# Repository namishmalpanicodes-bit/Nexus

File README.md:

# Nexus
Nexus is a smart desktop control centre. You have all your data from the task manager directly in front of you, like CPU, GPU, RAM, and storage one click and you know which app is consuming how Ram or storage. We also have a sidebar where we have features like notifications, screen time, and modes.

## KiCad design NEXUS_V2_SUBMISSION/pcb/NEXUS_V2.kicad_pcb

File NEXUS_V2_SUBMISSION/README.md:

# NEXUS V2 – desk control panel

NEXUS V2 is a desk control panel in the spirit of a Stream Deck. It has a 7" touchscreen, six programmable keys and a volume knob, and connects to a Mac or PC with a single USB-C cable. It is built around an **ESP32-P4** on a custom 4-layer PCB. No dev board is used.

## What it is and how to use it

1. Plug NEXUS into your computer with one USB-C cable. That single cable provides both power and data.
2. **Six keys (2 × 3):** each one triggers a computer shortcut. The firmware sends F13–F18, and the companion app maps each one to any action (launch an app, mute the mic, run a macro…).
3. **Knob:** turn it to change the volume and press it to mute or unmute.
4. **7" touchscreen:** shows CPU / RAM / GPU / storage, per-app usage, screen time and notifications. The sidebar switches between modes: **Coding, Study, Focus, Calm** (customisable).
5. **Tilt:** the screen sits on a weighted base with friction hinges. Tilt it to any angle from 15° to 70° and it stays there.

## Why I made it

I made NEXUS because I was struggling with small daily tasks. While browsing the internet, if I wanted to check my CPU, RAM, storage or any usage, I had to leave my browser and open Task Manager. To check my screen time, I had to go through Settings. To check my notifications, I had to open my phone or Gmail. And my device didn't have modes at all. That's why I created NEXUS.

Everything is in front of you: your CPU, GPU, RAM and storage. Click once and it tells you which app is using what. You get different modes (coding mode, study mode, focus mode, calm mode), and you can customise them however you want. Screen time shows you which app you used and for how long. You can enable notifications for any app you like, and disable them too.

## Hardware

| Block | Part |
|---|---|
| MCU | Espressif ESP32-P4NRW16X (QFN-104, 16 MB PSRAM) + 16 MB QSPI flash |
| Display | Waveshare 7-DSI-TOUCH-A, 720 × 1280 IPS, MIPI-DSI 2-lane, I2C touch |
| Keys | 6 × C&K PTS526 SPG15 SMTR2 LFS (320 gf), 19 mm pitch, pull-ups + firmware debounce |
| Encoder | EC11 incremental encoder with push switch |
| Power | USB-C 5 V → 2 × TLV62569 bucks (3V3 and VDD_HP core); internal LDOs for flash, PSRAM and MIPI |
| USB | HRO TYPE-C-31-M-12, USB 2.0 High-Speed to the ESP32-P4 OTG PHY |
| PCB | 54 × 118 mm, 4 layers (signal / GND / 3V3 / signal); KiCad DRC: 0 errors, 0 warnings, 0 unconnected |

## Enclosure

- **Form:** a slab on a stand. The screen is on the left and the keys and knob are on the right. The PCB sits *beside* the display, so the slab is only as thick as the display.
- **Base:** weighted with ~300 g of M12 steel washers in a pocket at the front. Two constant-torque hinges allow a 15–70° tilt.
- **USB-C plug:** an L-shaped plug sits hidden in a pocket in the base, and the cable exits at the rear.
- **CAD:** fully parametric Onshape FeatureScript (`cad/NEXUS_V2_slab_enclosure.fs`). Parameters: display depth, hinge hole spacing and screw size.
- **Printed parts (10):** front shell, back cover, base, 6 keycaps, 24 mm knob.
- **Materials:** matte PLA or PETG.

## Files

| Item | Location |
|---|---|
| STEP file for each part | `cad/NEXUS_V2_parts_STEP.zip` (10 parts) |
| Full assembly STEP | `cad/NEXUS_V2_full_assembly.step` |
| Onshape source | https://cad.onshape.com/documents/3eb919e14392e073160f8015/w/52b0d7887805c9e8dcde4446/e/a73d1369f3e2af2bd40e8e28 |
| KiCad project | `pcb/NEXUS_V2.kicad_pro`, `.kicad_sch`, `.kicad_pcb`, `.kicad_prl` + `NEXUS_V2_Custom.kicad_sym`, `NEXUS_V2_Footprints.pretty/`, `fp-lib-table`, `sym-lib-table` |
| Gerbers + drill | `pcb/gerbers.zip` |
| Firmware | `firmware/`: ESP-IDF project, untested (keys → F13–F18, knob → volume / mute) |
| BOM with links | `BOM.csv` |
| Pin map | `PIN_MAP.md` |
| Fabrication status | `pcb/FABRICATION_STATUS.txt` |

## Status and known issues (rev B)

- **Verified:** KiCad DRC is clean. The switch footprint was checked against the C&K datasheet. The encoder footprint matches the ALPS EC11 reference and the listing dimensions (6 mm D-shaft, M7 thread, 15 mm shaft, 15 × 12 mm body). The display outline and depth match the Waveshare drawing.
- **To confirm on the real parts before ordering boards:**
  - encoder pin spacing (caliper check)
  - display cable contact side, which decides the exact J1 connector part
  - hinge hole pattern
- **Rev C plan:**
  - rear-facing USB-C through the back cover
  - a branded encoder (Bourns PEC11R) for production
  - display UI firmware: MIPI-DSI + LVGL, plus a USB link to the companion app

## Bill of materials

Full list with links: [BOM.csv](BOM.csv). Prices in USD (INR prices converted at 1 USD = 94.85 INR).

| Product | Description | Link | Price (USD) |
|---|---|---|---|
| Display | Waveshare 7-DSI-TOUCH-A. 7in 720x1280 IPS MIPI-DSI touch display; includes DSI-Cable-12cm + 5V power cable. Already owned. | [link](https://zbotic.in/product/waveshare-7inch-dsi-capacitive-touch-display/) | 67.93 |
| Rotary encoder | FlyRobo EC11 15 mm half-shaft SKU 3370. Incremental encoder with push switch (volume / mute). Price = Rs 47 encoder + Rs 100 FlyRobo delivery. | [link](https://www.flyrobo.in/ec11-rotary-encoder-half-shaft-handle-potentiometer-15mm) | 1.55 |
| MCU | ESP32-P4NRW16X. Espressif ESP32-P4, QFN-104, 16 MB PSRAM in package | [link](https://www.lcsc.com/search?q=ESP32-P4NRW16X) | 4.74 |
| Flash | W25Q128JVSIQ. 16 MB QSPI flash, SOIC-8 208 mil | [link](https://www.lcsc.com/search?q=W25Q128JVSIQ) | 2.18 |
| Buck regulator x2 | TLV62569DBVR. 3 A step-down (core VDD_HP and 3V3) | [link](https://www.ti.com/product/TLV62569) | 0.13 |
| Inductor x2 | Murata DFE252012F-2R2M. 2.2 uH, Isat >= 3 A, 2520 | [link](https://www.lcsc.com/search?q=DFE252012F-2R2M) | 0.07 |
| Crystal | 40 MHz 3225. 40 MHz, CL 10 pF, +-10 ppm, 3225 | [link](https://www.lcsc.com/search?q=40MHz%203225%20crystal%2010pF) | 0.05 |
| USB-C receptacle | HRO TYPE-C-31-M-12. 16-pin USB 2.0 Type-C, LCSC C165948 | [link](https://lcsc.com/product-detail/C165948.html) | 0.10 |
| FPC connector | Amphenol SFW15R-1STAE1LF (or Molex 52207-1560). 15-pin 1.0 mm FPC ZIF (display DSI). Final pick depends on cable contact side | [link](https://lioncircuits.com/parts/SFW15R-1STE1LF) | 0.95 |
| Tactile switch x8 | C&K PTS526 SPG15 SMTR2 LFS, Robu SKU R185029, USD 0.14 each. 6 keys + BOOT and RESET. Robu delivery is free above Rs 999; below that it is added at checkout. | [link](https://robu.in/product/pts526-spg15-smtr2-lfs-ck-5-2mm-1-5mm-5-2mm-320gf-smd-tactile-switches-rohs/) | 1.10 |
| TVS diode | SMF5.0A. 5 V TVS on VBUS, SOD-123F | [link](https://www.lcsc.com/search?q=SMF5.0A) | 0.05 |
| ESD diode x2 | TI TPD1E0B04. 0.13 pF bidirectional ESD (USB D+/D-) | [link](https://www.lcsc.com/search?q=TPD1E0B04) | 0.33 |
| PTC fuse | Bourns MF-MSMF110. 1.1 A hold, 1812 | [link](https://www.lcsc.com/search?q=MF-MSMF110) | 0.03 |
| LED x2 | 0603 LED green / blue. Power and user LEDs | [link](https://www.lcsc.com/search?q=0603%20LED) | 0.03 |
| Capacitor 10uF x6 | 10uF 10V X5R 0805 | [link](https://www.lcsc.com/search?q=10uF%200805%2010V%20X5R) | 0.09 |
| Capacitor 22uF x3 | 22uF 10V X5R 0805 | [link](https://www.lcsc.com/search?q=22uF%200805%2010V) | 0.16 |
| Capacitor 4.7uF x2 | 4.7uF 10V X5R 0603 | [link](https://www.lcsc.com/search?q=4.7uF%200603%2010V) | 0.03 |
| Capacitor 1uF x6 | 1uF 10V X5R 0402 LCSC sells these in strips of 100, so the price is for 100 pcs. | [link](https://www.lcsc.com/search?q=1uF%200402%2010V) | 0.23 |
| Capacitor 0.1uF x23 | 0.1uF 16V X7R 0402 LCSC sells these in strips of 100, so the price is for 100 pcs. | [link](https://www.lcsc.com/search?q=100nF%200402%2016V%20X7R) | 0.16 |
| Capacitor 10nF x2 | 10nF 16V X7R 0402 LCSC sells these in strips of 100, so the price is for 100 pcs. | [link](https://www.lcsc.com/search?q=10nF%200402) | 0.16 |
| Capacitor 22pF | 22pF C0G 0402 LCSC sells these in strips of 100, so the price is for 100 pcs. | [link](https://www.lcsc.com/search?q=22pF%200402%20C0G) | 0.16 |
| Capacitor 15pF x2 | 15pF C0G 0402. Crystal load (tune) LCSC sells these in strips of 100, so the price is for 100 pcs. | [link](https://www.lcsc.com/search?q=15pF%200402%20C0G) | 0.16 |
| Resistor 10k x12 | 10k 1% 0402. Pull-ups (buttons, encoder, straps) LCSC sells these in strips of 100, so the price is for 100 pcs. | [link](https://www.lcsc.com/search?q=10k%200402%201%) | 0.05 |
| Resistor 5.1k x2 | 5.1k 1% 0402. USB-C CC pull-downs LCSC sells these in strips of 100, so the price is for 100 pcs. | [link](https://www.lcsc.com/search?q=5.1k%200402) | 0.05 |
| Resistor 2.2k x2 | 2.2k 0402. I2C pull-ups LCSC sells these in strips of 100, so the price is for 100 pcs. | [link](https://www.lcsc.com/search?q=2.2k%200402) | 0.05 |
| Resistor 1k x2 | 1k 0603. LED resistors LCSC sells these in strips of 100, so the price is for 100 pcs. | [link](https://www.lcsc.com/search?q=1k%200603) | 0.05 |
| Resistor (dividers) x6 | 453k / 100k / 499k x2 / 4.02k / 1M, 1% 0402. Buck feedback, DSI REXT, misc LCSC sells these in strips of 100, so the price is for 100 pcs. | [link](https://www.lcsc.com/search?q=0402%201%%20resistor) | 0.05 |
| Pin header 1x8 (J3) | Shekki 1x40 single-row male header, 2.54 mm, single strip. J3 programming header; cut 8 pins. | [link](https://www.amazon.in/dp/B0H467TGFM) | 0.52 |
| Pin header 1x3 right-angle (J4) | Electronic Spices 1x40 right-angle (90 deg) male header, pack of 5 (smallest pack on Amazon). J4 display 5 V header; cut 3 pins from one strip. | [link](https://www.amazon.in/dp/B0BG7KGL77) | 0.84 |
| PCB x5 | NEXUS V2 custom PCB rev B, 4-layer, 118 x 54 mm, 1.6 mm, ENIG. Manufacturing files: pcb/gerbers.zip in this repo (upload pcb/gerbers.zip at the JLCPCB link to get this exact quote: 5 pcs, 4 layers, ENIG = USD 84.00). JLCPCB minimum order is 5 boards; 1 is used, 4 are spares. | [link](https://cart.jlcpcb.com/quote) | 84.00 |
| Friction hinges | TAODAN torque friction hinges, 1 left + 1 right, mounting screws included. Holds the slab at any tilt angle. | [link](https://www.amazon.in/dp/B0BNH8985Y) | 23.21 |
| Base weight | 50 x M12 SS304 flat washers (DIN 125, about 6 g each, about 300 g total). Stacked in the pocket under the base to stop the device tipping. | [link](https://www.amazon.in/dp/B0H122NK8H) | 2.41 |
| Anti-slip feet | nuoshen clear self-adhesive rubber feet, 100 pcs (4 used under the base). | [link](https://www.amazon.in/dp/B0F7FKDTF9) | 1.17 |
| USB-C cable | Verilux 3 m USB-C to USB-C, 90 deg right-angle end, 480 Mbps data + 100 W. The L end plugs into NEXUS inside the base. | [link](https://www.amazon.in/dp/B0F942Z4LY) | 6.32 |
| 23AWG single-strand wire (black+red, 1+1 m) (tool) | CBL-QC0413. Assembly / testing tool. Already owned. | [link](https://quartzcomponents.com/search?q=CBL-QC0413) | 0.31 |
| Jumper wire combo M-M / M-F / F-F (10 each) (tool) | CBL-QC0613. Assembly / testing tool. Already owned. | [link](https://quartzcomponents.com/search?q=CBL-QC0613) | 0.65 |
| DT830D digital multimeter (tool) | TLS-QC0298. Assembly / testing tool. Already owned. | [link](https://quartzcomponents.com/search?q=TLS-QC0298) | 2.30 |
| MB102 breadboard 830 points (tool) | TLS-QC0412. Assembly / testing tool. Already owned. | [link](https://quartzcomponents.com/search?q=TLS-QC0412) | 0.85 |
| Solder wire 5 g (tool) x2 | TLS-QC0863. Assembly / testing tool. Already owned. | [link](https://quartzcomponents.com/search?q=TLS-QC0863) | 0.57 |
| RMA-223 solder flux paste (tool) | TLS-QC0864. Assembly / testing tool. Already owned. | [link](https://quartzcomponents.com/search?q=TLS-QC0864) | 0.46 |
| 25 W soldering iron (tool) | TLS-QC1041. Assembly / testing tool. Already owned. | [link](https://quartzcomponents.com/search?q=TLS-QC1041) | 1.03 |
| Soldering iron stand (tool) | TLS-QC2658. Assembly / testing tool. Already owned. | [link](https://quartzcomponents.com/search?q=TLS-QC2658) | 0.30 |
| Wire stripper / cutter 130 mm (tool) | TLS-QC3658. Assembly / testing tool. Already owned. | [link](https://quartzcomponents.com/search?q=TLS-QC3658) | 0.44 |
| SMT stencil | JLCPCB stencil, non-framework, top + bottom on one sheet, 0.12 mm, electropolished. Needed by the vendor to apply solder paste for the ESP32-P4 | [link](https://jlcpcb.com/pcb-stencil) | 7.00 |
| Double-sided foam tape | 3M Scotch heavy-duty double-sided foam tape (holds 4.5 kg per metre). Holds the display in the front shell and seals the washers into the base pocket. | [link](https://www.amazon.in/dp/B00N1U9AJS) | 1.80 |
| Shipping + customs (JLCPCB + LCSC) | PCBs, stencil and LCSC parts shipped from China in one combined parcel. Courier fee and Indian customs duty are calculated by JLCPCB/LCSC at checkout. | [link](https://jlcpcb.com) | At checkout |
| TOTAL build cost | Everything above except the tools and the shipping row. |  | 207.91 |
| Tools (already owned) | Not part of the build cost |  | 6.90 |

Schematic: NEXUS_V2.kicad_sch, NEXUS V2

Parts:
C1, C2, C9, C109, C110, C111: 10uF; C_0805; MPN 10uF 10V X5R 0805
C3, C10, C100, C101, C102, C103, C104, C105, C106, C107, C108, C112, C115, C116, C117, C118, C119, C121, C122, C125: 0.1uF; R_0402; MPN 0.1uF 16V X7R 0402
C4, C5, C7: 22uF; C_0805; MPN 22uF 10V X5R 0805
C6, C114: 4.7uF; R_0603; MPN 4.7uF 10V X5R 0603
C8: 22pF; R_0402; MPN 22pF C0G 0402
C11, C12: 15pF; R_0402; MPN 15pF C0G 0402 (tune)
C13, C120, C123, C124, C127, C128: 1uF; R_0402; MPN 1uF 10V X5R 0402
C14, C15, C16: 0.1uF; R_0402; MPN 0.1uF 0402
C113, C126: 10nF; R_0402; MPN 10nF 16V X7R 0402
D1: SMF5.0A; D_SOD123F; MPN SMF5.0A (5V TVS)
D2, D3: TPD1E0B04; R_0402; MPN TI TPD1E0B04 (0.13pF bidir ESD)
ENC1: EC11; MPN FlyRobo EC11 15 mm half-shaft SKU 3370 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
F1: PTC 1.1A; F_1812; MPN 1812 PTC 1.1A hold (e.g. Bourns MF-MSMF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
J1: DSI 15P; FPC15_P1.00mm_Generic; MPN 15p 1.0mm FPC ZIF (Hirose FH12-15S-1SH 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
J2: USB-C 16P; USB_C_HRO_TYPE-C-31-M-12_Recon; MPN HRO TYPE-C-31-M-12
J3: DEBUG; HDR_1x8; MPN 2.54mm 1x8 header - fit from BACK side 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
J4: DISP_5V; HDR_1x3; MPN 2.54mm 1x3 RIGHT-ANGLE header (display 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
L1: 2.2uH; L_2520; MPN 2.2uH Isat>=3A 2520 (e.g. Murata DFE252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
L2: 2.2uH; L_2520; MPN 2.2uH Isat>=3A 2520
LED1: LED 3V3; R_0603; MPN 0603 LED green
LED2: LED USER; R_0603; MPN 0603 LED blue
MH1, MH2, MH3, MH4: M3; MH_M3; MPN M3 mounting hole
R1, R2: 5.1k; R_0402; MPN 5.1k 1% 0402
R3: 453k; R_0402; MPN 453k 1% 0402
R4: 100k; R_0402; MPN 100k 1% 0402
R5, R15: 1k; R_0603; MPN 1k 0603
R6, R7: 499k; R_0402; MPN 499k 1% 0402
R8, R9, R10: 10k; R_0402; MPN 10k 0402
R11, R12: 2.2k; R_0402; MPN 2.2k 0402
R13: 4.02k; R_0402; MPN 4.02k 1% 0402
R14: 1M; R_0402; MPN 1M 0402
R16, R17, R18, R19, R20, R21: 10k; R_0402; MPN 10k 1% 0402 (button pull-up)
R22, R23, R24: 10k; R_0402; MPN 10k 1% 0402 (encoder pull-up)
SW1: BTN1; PTS526; MPN C&K PTS526 SPG15 SMTR2 LFS (320 gf, gro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
SW2: BTN2; PTS526; MPN C&K PTS526 SPG15 SMTR2 LFS (320 gf, gro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
SW3: BTN3; PTS526; MPN C&K PTS526 SPG15 SMTR2 LFS (320 gf, gro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
SW4: BTN4; PTS526; MPN C&K PTS526 SPG15 SMTR2 LFS (320 gf, gro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
SW5: BTN5; PTS526; MPN C&K PTS526 SPG15 SMTR2 LFS (320 gf, gro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
SW6: BTN6; PTS526; MPN C&K PTS526 SPG15 SMTR2 LFS (320 gf, gro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
SW7: BOOT; PTS526; MPN C&K PTS526 SPG15 SMTR2 LFS (320 gf, gro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
SW8: RESET; PTS526; MPN C&K PTS526 SPG15 SMTR2 LFS (320 gf, gro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
U1: ESP32-P4NRW16X; ESP32-P4_QFN104_Rot180; MPN ESP32-P4NRW16X
U2: TLV62569DBV; SOT23_5; MPN TLV62569DBVR (core buck)
U3: TLV62569DBV; SOT23_5; MPN TLV62569DBVR (3V3 buck)
U4: W25Q128JVSIQ; SOIC8_208; MPN W25Q128JVSIQ 3.3V 16MB
Y1: 40MHz; XTAL_3225; MPN 40MHz 3225 CL10pF +-10ppm

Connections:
/+3V3: C4.1, C5.1, C6.1, C100.1, C101.1, C102.1, C103.1, C104.1, C105.1, C106.1, C107.1, C108.1, C109.1, C110.1, C111.1, C112.1, C113.1, C114.1, J1.14 (3V3), J1.15 (3V3), J3.1 (3V3), L1.2, R3.1, R5.1, R9.2, R10.2, R11.2, R12.2, R16.2, R17.2, R18.2, R19.2, R20.2, R21.2, R22.2, R23.2, R24.2, U1.9 (VDD_LP), U1.21 (VDD_IO_0), U1.51 (VDD_USBPHY), U1.62 (VDD_IO_4), U1.75 (VDD_LDO), U1.77 (VDD_DCDCC), U1.85 (VDD_IO_5), U1.96 (VDD_IO_6), U1.101 (VDD_ANA), U1.102 (VDD_BAT), U2.4 (VIN)
/+5V: C1.1, C2.1, C3.1, F1.2, J4.1 (5V), J4.2 (5V), U3.1 (EN), U3.4 (VIN)
/BOOT: J3.8 (BOOT), R10.1, SW7.1 (A1), SW7.2 (A2), U1.66 (GPIO35)
/BTN1: R16.1, SW1.1 (A1), SW1.2 (A2), U1.25 (GPIO23)
/BTN2: R17.1, SW2.1 (A1), SW2.2 (A2), U1.23 (GPIO21)
/BTN3: R18.1, SW3.1 (A1), SW3.2 (A2), U1.20 (GPIO19)
/BTN4: R19.1, SW4.1 (A1), SW4.2 (A2), U1.18 (GPIO17)
/BTN5: R20.1, SW5.1 (A1), SW5.2 (A2), U1.16 (GPIO15)
/BTN6: R21.1, SW6.1 (A1), SW6.2 (A2), U1.14 (GPIO13)
/CC1: J2.A5 (CC1), R1.1
/CC2: J2.B5 (CC2), R2.1
/CHIP_PU: C13.1, J3.7 (EN), R9.1, SW8.1 (A1), SW8.2 (A2), U1.103 (CHIP_PU)
/CORE_FB: C8.2, R6.2, R7.1, U1.78 (FB_DCDC), U2.5 (FB)
/DCDC_EN: U1.79 (EN_DCDC), U2.1 (EN)
/DSI_CKN: J1.5 (CK_N), U1.37 (DSI_CLKN)
/DSI_CKP: J1.6 (CK_P), U1.38 (DSI_CLKP)
/DSI_D0N: J1.8 (D0_N), U1.40 (DSI_DATAN0)
/DSI_D0P: J1.9 (D0_P), U1.39 (DSI_DATAP0)
/DSI_D1N: J1.2 (D1_N), U1.36 (DSI_DATAN1)
/DSI_D1P: J1.3 (D1_P), U1.35 (DSI_DATAP1)
/DSI_REXT: R13.1, U1.34 (DSI_REXT)
/ENC_A: C14.1, ENC1.A, R22.1, U1.1 (GPIO1)
/ENC_B: C15.1, ENC1.B, R23.1, U1.2 (GPIO2)
/ENC_SW: C16.1, ENC1.S1 (SW1), R24.1, U1.3 (GPIO3)
/FB3: R3.2, R4.1, U3.5 (FB)
/FL_CK: U1.32 (FLASH_CK), U4.6 (CLK)
/FL_CS: R8.1, U1.27 (FLASH_CS), U4.1 (CS#)
/FL_D: U1.33 (FLASH_D), U4.5 (DI(IO0))
/FL_HD: U1.31 (FLASH_HOLD), U4.7 (HOLD#(IO3))
/FL_Q: U1.28 (FLASH_Q), U4.2 (DO(IO1))
/FL_WP: U1.29 (FLASH_WP), U4.3 (WP#(IO2))
/GND: C1.2, C2.2, C3.2, C4.2, C5.2, C6.2, C7.2, C9.2, C10.2, C11.2, C12.2, C13.2, C14.2, C15.2, C16.2, C100.2, C101.2, C102.2, C103.2, C104.2, C105.2, C106.2, C107.2, C108.2, C109.2, C110.2, C111.2, C112.2, C113.2, C114.2, C115.2, C116.2, C117.2, C118.2, C119.2, C120.2, C121.2, C122.2, C123.2, C124.2, C125.2, C126.2, C127.2, C128.2, D1.2, D2.2, D3.2, ENC1.C (COM), ENC1.MP (MOUNT), ENC1.S2 (SW2), J1.1 (GND), J1.4 (GND), J1.7 (GND), J1.10 (GND), J1.13 (GND), J1.MP (SHIELD), J2.A1B12 (GND), J2.B1A12 (GND), J2.S1 (SHIELD), J3.2 (GND), J4.3 (GND), LED1.1, LED2.1, R1.2, R2.2, R4.2, R7.2, R13.2, R14.2, SW1.3 (B1), SW1.4 (B2), SW1.5 (SHIELD1), SW1.6 (SHIELD2), SW2.3 (B1), SW2.4 (B2), SW2.5 (SHIELD1), SW2.6 (SHIELD2), SW3.3 (B1), SW3.4 (B2), SW3.5 (SHIELD1), SW3.6 (SHIELD2), SW4.3 (B1), SW4.4 (B2), SW4.5 (SHIELD1), SW4.6 (SHIELD2), SW5.3 (B1), SW5.4 (B2), SW5.5 (SHIELD1), SW5.6 (SHIELD2), SW6.3 (B1), SW6.4 (B2), SW6.5 (SHIELD1), SW6.6 (SHIELD2), SW7.3 (B1), SW7.4 (B2), SW7.5 (SHIELD1), SW7.6 (SHIELD2), SW8.3 (B1), SW8.4 (B2), SW8.5 (SHIELD1), SW8.6 (SHIELD2), U1.105 (GND), U2.2 (GND), U3.2 (GND), U4.4 (GND), Y1.2 (GND1), Y1.4 (GND2)
/I2C_SCL: J1.11 (SCL), R11.1, U1.57 (GPIO28)
/I2C_SDA: J1.12 (SDA), R12.1, U1.58 (GPIO29)
/LED_A: LED1.2, R5.2
/LED_B: LED2.2, R15.2
/LED_USER: R15.1, U1.5 (GPIO5)
/SW2: L2.1, U2.3 (SW)
/SW3: L1.1, U3.3 (SW)
/USB_DM: D3.1, J2.A7 (D-(A7)), J2.B7 (D-(B7)), U1.49 (USB_DM)
/USB_DP: D2.1, J2.A6 (D+(A6)), J2.B6 (D+(B6)), R14.1, U1.50 (USB_DP)
/USB_JTAG_DM: J3.5 (JTAG_D-), U1.52 (GPIO24)
/USB_JTAG_DP: J3.6 (JTAG_D+), U1.53 (GPIO25)
/VBUS: D1.1, F1.1, J2.A4B9 (VBUS), J2.B4A9 (VBUS)
/VDDO_FLASH: C10.1, C119.1, C120.1, R8.2, U1.30 (VDD_FLASHIO), U1.71 (VDDO_FLASH), U4.8 (VCC)
/VDDO_PSRAM: C121.1, C122.1, C123.1, C124.1, U1.59 (VDD_PSRAM_0), U1.67 (VDD_PSRAM_1), U1.72 (VDDO_PSRAM)
/VDD_HP: C7.1, C8.1, C9.1, C115.1, C116.1, C117.1, C118.1, L2.2, R6.1, U1.26 (VDD_HP_0), U1.54 (VDD_HP_1), U1.76 (VDD_HP_2), U1.91 (VDD_HP_3)
/VDD_MIPI: C125.1, C126.1, C127.1, C128.1, U1.41 (VDD_MIPI_DPHY), U1.73 (VDDO_3)
/XTAL_N: C11.1, U1.99 (XTAL_N), Y1.1 (XIN)
/XTAL_P: C12.1, U1.100 (XTAL_P), Y1.3 (XOUT)

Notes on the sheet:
VDD_HP buck: R6/R7 499k + C8 22pF populated for ESP32-P4 chip revision v3.0 (P4X). Do not populate for v1.x silicon.
CORE BUCK VDD_HP (TLV62569)
Display: Waveshare 7-DSI-TOUCH-A (720x1280). J1 = Raspberry Pi 4 15-pin DSI pinout (GND,D1N,D1P,GND,CKN,CKP,GND,D0N,D0P,GND,SCL,SDA,GND,3V3,3V3); use Waveshare DSI-Cable-12cm.
Display 5V (>=0.5A) comes from J4 (1x3 right-angle: 5V,5V,GND = RPi pins 2/4/6 order), NOT through the DSI cable. Check plug orientation before power-up.
ERC: PWR_FLAGs added; ERC clean except one cosmetic off-grid pin in the ESP32-P4 library symbol. DRC: 0 errors / 0 warnings (26 Nov 2026).
BUTTONS / ENCODER / LEDS
3V3 BUCK (TLV62569)
LDO3 (VDDO_3) must be configured to 2.5V in firmware to power VDD_MIPI_DPHY. GPIO28/29 = I2C to display touch/backlight.
ESP32-P4 DECOUPLING (bottom side)
FLASH / CLOCK / RESET / BOOT
POWER FLAGS (ERC: these nets are driven by regulators / USB)
USB-C INPUT / PROTECTION
DISPLAY + DEBUG CONNECTORS
NEXUS V2 - ESP32-P4 desk control panel. Generated schematic; connectivity is by net labels (same name = same net).

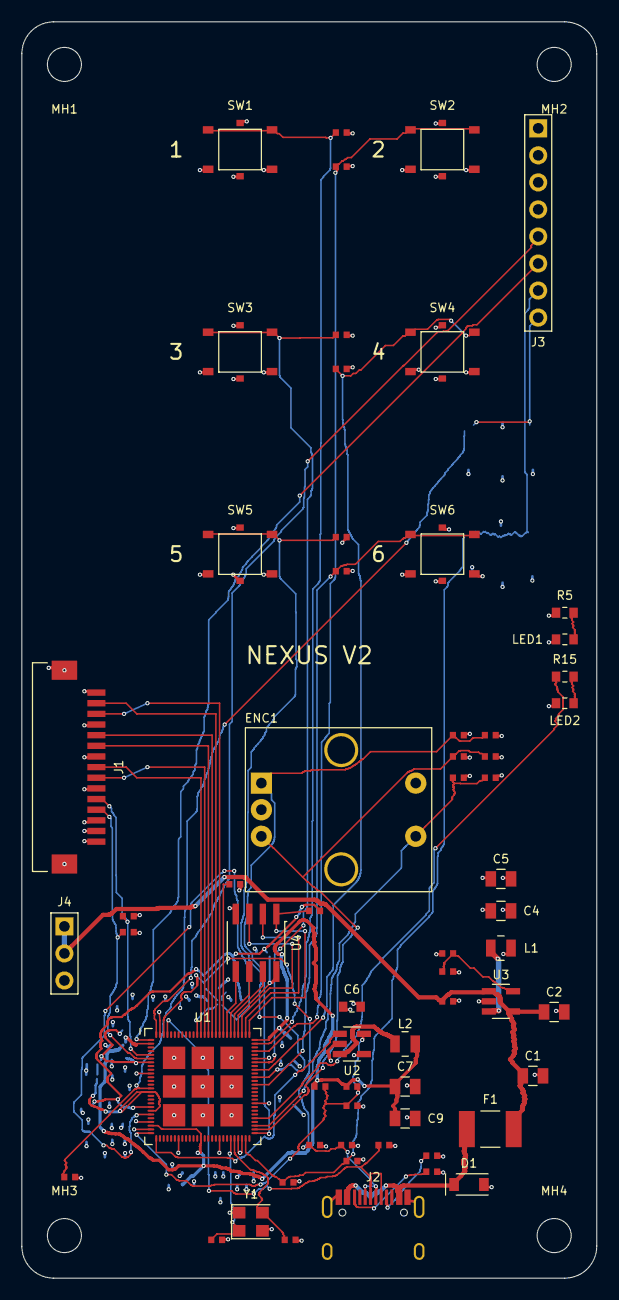
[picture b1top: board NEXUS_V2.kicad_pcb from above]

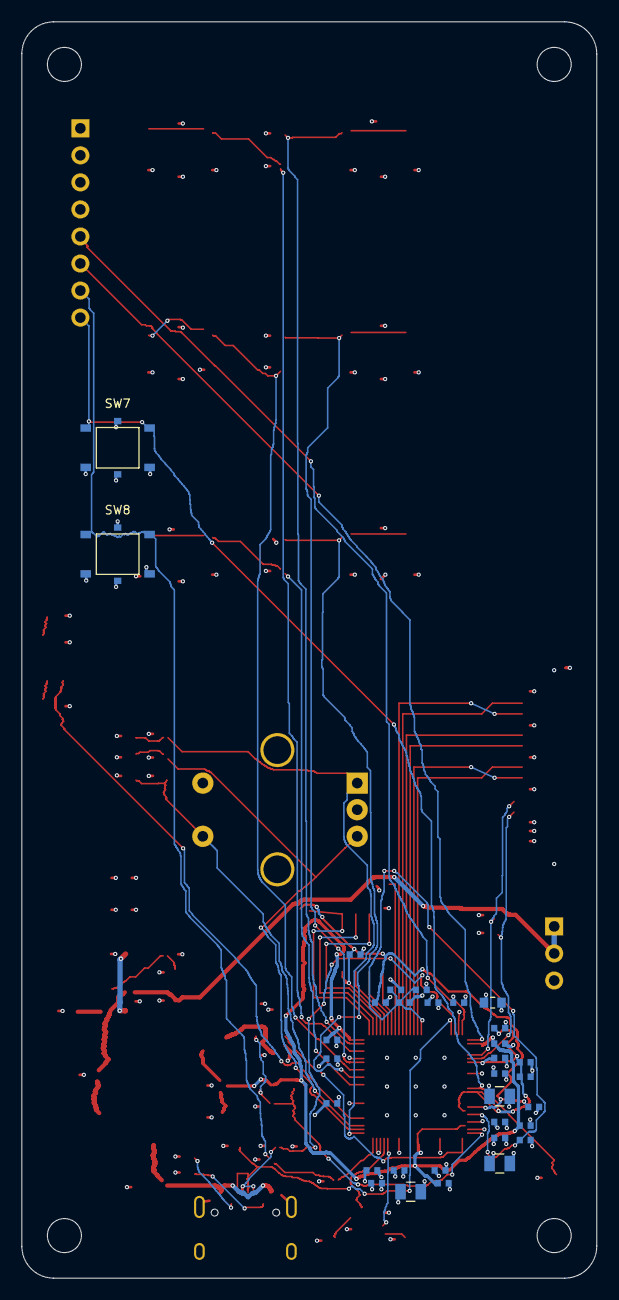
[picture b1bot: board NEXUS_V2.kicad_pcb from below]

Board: 4 copper layers, 54.0 x 118.0 mm, 99 parts (32 on the bottom side), 50 nets.

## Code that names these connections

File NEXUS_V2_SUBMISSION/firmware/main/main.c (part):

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
/* ---------------- pins (PIN_MAP.md) ---------------- */
static const gpio_num_t KEY_PINS[6] = {GPIO_NUM_23, GPIO_NUM_21, GPIO_NUM_19, GPIO_NUM_17, GPIO_NUM_15, GPIO_NUM_13};
#define ENC_A_PIN   GPIO_NUM_1
#define ENC_B_PIN   GPIO_NUM_2
#define ENC_SW_PIN  GPIO_NUM_3
#define LED_PIN     GPIO_NUM_5
#define I2C_SCL_PIN GPIO_NUM_28
#define I2C_SDA_PIN GPIO_NUM_29
#define BL_I2C_ADDR 0x45      /* Waveshare 7-DSI-TOUCH-A backlight controller */
#define BL_REG      0x96

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    ESP_ERROR_CHECK(pcnt_unit_set_glitch_filter(enc_unit, &filter));

    pcnt_channel_handle_t ch_a, ch_b;
    pcnt_chan_config_t cfg_a = {.edge_gpio_num = ENC_A_PIN, .level_gpio_num = ENC_B_PIN};
    pcnt_chan_config_t cfg_b = {.edge_gpio_num = ENC_B_PIN, .level_gpio_num = ENC_A_PIN};
    ESP_ERROR_CHECK(pcnt_new_channel(enc_unit, &cfg_a, &ch_a));
    ESP_ERROR_CHECK(pcnt_new_channel(enc_unit, &cfg_b, &ch_b));
    ESP_ERROR_CHECK(pcnt_channel_set_edge_action(ch_a, PCNT_CHANNEL_EDGE_ACTION_DECREASE, PCNT_CHANNEL_EDGE_ACTION_INCREASE));
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
static void inputs_init(void)
{
    uint64_t mask = (1ULL << ENC_SW_PIN);
    for (int i = 0; i < 6; i++) mask |= (1ULL << KEY_PINS[i]);
    gpio_config_t in = {.pin_bit_mask = mask, .mode = GPIO_MODE_INPUT, .pull_up_en = GPIO_PULLUP_ENABLE};
    ESP_ERROR_CHECK(gpio_config(&in));
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    /* Backlight on (Waveshare: register 0x96 at I2C address 0x45, 0..255) */
    i2c_master_bus_handle_t bus;
    i2c_master_bus_config_t bus_cfg = {
        .i2c_port = I2C_NUM_0, .sda_io_num = I2C_SDA_PIN, .scl_io_num = I2C_SCL_PIN,
        .clk_source = I2C_CLK_SRC_DEFAULT, .glitch_ignore_cnt = 7,
    };
    ESP_ERROR_CHECK(i2c_new_master_bus(&bus_cfg, &bus));
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    for (;;) {
        TickType_t now = xTaskGetTickCount();
        for (int i = 0; i < 7; i++) {
            gpio_num_t pin = (i < 6) ? KEY_PINS[i] : ENC_SW_PIN;
            bool raw = (gpio_get_level(pin) == 0);              /* active LOW */
            if (raw != last_raw[i]) { last_raw[i] = raw; changed_at[i] = now; }
            if (raw != stable[i] && (now - changed_at[i]) >= pdMS_TO_TICKS(DEBOUNCE_MS)) {
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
